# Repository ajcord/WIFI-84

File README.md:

# WIFI-84
*Wi-Fi Interface Furnishing Internet for TI-84*

## Overview

This project aims to provide direct Internet access to TI-84 calculators
using an inexpensive ESP8266 module as a wireless modem.
It supports calculators with I/O ports, i.e. those up to the TI-84+CSE.

## Architecture

The project consists of four main parts:

1. A physical interface between the calculator and ESP8266
2. A driver for communicating between them
3. A high-level networking API exposed to calculator programs
4. A small collection of sample utilities using the API

### Physical interface

The adapter is powered from the calculator's USB port for convenience.
It could probably also be powered from e.g. a USB phone charger,
as long as the power supply is not noisy.
The USB's 5V gets converted to 3.3V using an efficient switching regulator
to save battery.

For communication, the adapter uses the I/O port for simplicity.
Ideally, it would use the USB port for forward compatibility and since
it already uses it for power;
however, writing a USB driver would be a lot of effort for very little gain,
considering that the TI-84+CE uses a completely different USB controller.

It would be nice to have the adapter plug directly into the calculator,
but I can't seem to find any 2.5mm male headphone connectors,
and the only USB mini-B male connector I found is vertical.
Instead, the adapter plugs in using cables,
but is laid out to make it easy to switch to a plug-oriented design later.
See the `hardware` folder for the schematic and circuit board.

### Driver

The ESP8266 runs firmware that directly communicates with the calculator
using the [ArTICL](https://github.com/KermMartian/ArTICL) library.
It acts as a CBL2 device to make communication easy with TI Basic programs.

The calculator does not need a driver since it uses the CBL2
Get( and Send( commands.
It does, however, need a way to turn on and off the USB port.

### API

The API exposed to the calculator is still in flux,
but it will provide similar capabilities to the ESP8266's default AT firmware.
The calculator will be able to send string variables containing API calls,
and then it will request another variable to get the result (if applicable).

The calculator will send token strings as commands
in order to save program space.
The ESP8266 will respond with token strings or real numbers,
depending on the call.

### Utilities

There will need to be a program to allow the user to connect to
nearby Wi-Fi networks.
It can be as simple as a menu of SSIDs.
By including such a program, applications won't need to
reinvent the wheel, and the connection can be managed centrally.

Also, a tool like wget/curl would be useful for testing.
It would probably have to include its own viewer to display the response
incrementally due to limited RAM.
For HTML, maybe it could have the option to display it with tags stripped
so that it looks sort of like a webpage.

In the future, it would be really cool to have the ESP8266 pre-render webpages
and have the calculator display them screen by screen.
A Slack client would also be neat.

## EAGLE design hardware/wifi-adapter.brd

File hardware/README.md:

# Hardware

## Schematic

See `wifi-adapter.sch` for the schematic,
or `wifi-adapter.pdf` if you don't have EAGLE.

## Bill of Materials

This DigiKey cart contains all the components needed in the project:
[cart](http://www.digikey.com/short/3r35nm)

In addition, you will need to manufacture a circuit board using
`wifi-adapter.brd`.
[OSH Park](https://oshpark.com) is a good place to order it.

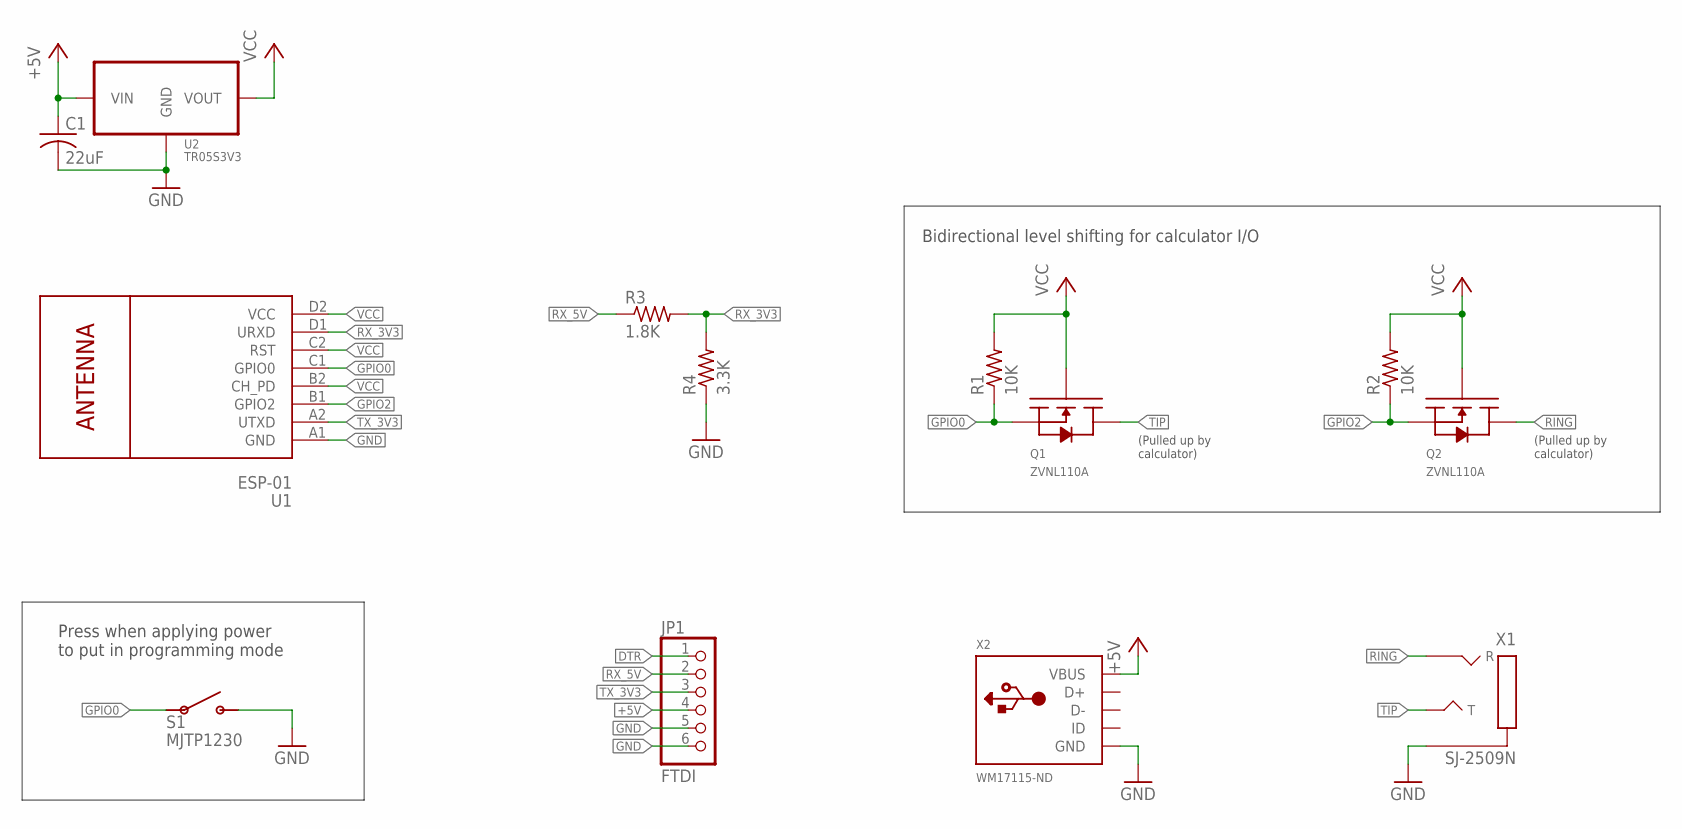
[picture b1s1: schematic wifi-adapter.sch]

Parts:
C1: 22uF; C025-025X050
JP1: FTDI; 1X06
Q1, Q2: ZVNL110A; E-LINE-RA
R1, R2: 10K; 0207/10
R3: 1.8K; 0207/10
R4: 3.3K; 0207/10
S1: MJTP1230; TACTILE-BUTTON-MJTP1230
U1: ESP-01; WIRELESS-WIFI-ESP-01
U2: TR05S3V3; 3-SIP
X1: SJ-2509N
X2: WM17115-ND; USB-MINI-B

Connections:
+5V: C1.1, JP1.4, U2.P$1 (VIN), X2.VBUS
DTR: JP1.1
GND: C1.2, JP1.5, JP1.6, R4.1, S1.P$2 (3), S1.P$4 (3), U1.A1 (GND), U2.P$2 (GND), X1.P$1, X2.GND, X2.GND1 (GND), X2.GND4 (GND)
GPIO0: Q1.P$3 (S), R1.1, S1.P$1 (1), S1.P$3 (1), U1.C1 (GPIO0)
GPIO2: Q2.P$3 (S), R2.1, U1.B1 (GPIO2)
RING: Q2.P$1 (D), X1.P$2
RX_3V3: R3.2, R4.2, U1.D1 (URXD)
RX_5V: JP1.2, R3.1
TIP: Q1.P$1 (D), X1.P$3
TX_3V3: JP1.3, U1.A2 (UTXD)
VCC: Q1.P$2 (G), Q2.P$2 (G), R1.2, R2.2, U1.B2 (CH_PD), U1.C2 (RST), U1.D2 (VCC), U2.P$3 (VOUT)

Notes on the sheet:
(Pulled up by calculator)
Bidirectional level shifting for calculator I/O
Press when applying power to put in programming mode

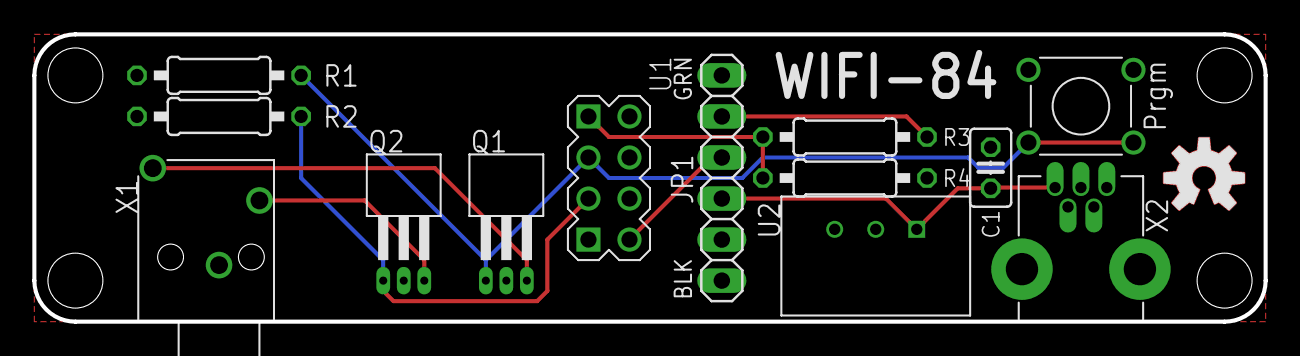
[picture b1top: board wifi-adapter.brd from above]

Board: 2 copper layers, 76.2 x 17.8 mm, 15 parts (0 on the bottom side), 10 nets.

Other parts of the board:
U$1: OSHW-LOGO-M
U$2: OSHW-LOGO-M_COPPER

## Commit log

2016-12-30 Updated architecture ideas
2017-01-02 First real commit
2017-01-03 Improved CSV generation
2017-01-03 Greatly simplified token parsing by assuming tokens are valid and removing toString
2017-01-03 Removed unnecessary datalen
2017-01-03 Fixed Connected to return 1 or 0, not enum
2017-01-03 Enum-ified token prefixes
2017-01-03 Fixed parameter name
2017-01-03 Added a token string builder
2017-01-03 Use StringBuilder instead of hacky stuff
2017-01-03 Rename insert() to append() for clarity
2017-01-03 Added length checking to StringBuilder
2017-01-03 Moved token list to separate file
2017-01-03 Fixed token casting
2017-01-03 Compacted case statements
2017-01-03 Switched to unsigned chars
2017-01-03 Fixed a couple of character conversion mistakes
2017-01-04 Removed StringBuilder
2017-01-04 Minor style changes
2017-01-04 Added some debug printing
2017-01-04 Added ability to connect to a network
2017-01-04 Made Connected return more detailed information
2017-01-04 Added comments and tweaked API
2017-01-04 Added basic TCP and UDP client commands
2017-01-04 Switched tokens for sending/receiving on a connection
2017-01-04 Added HTTP GET
2017-01-04 Fixed String conversion
2017-01-04 Added debugging output
2017-01-04 Added ability to see which network is connected to
2017-01-05 Added connection management program
2017-01-06 Added timeout, default to current network, and fixed syntax errors
2017-01-08 Added HTTP POST
2017-01-08 Added basic wget utility
2017-01-08 Added simplistic HTML viewer

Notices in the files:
parts and their libraries:
diy-modules: Released under the Creative Commons Attribution 4.0 International License: http://creativecommons.org/licenses/by/4.0
SparkFun-Aesthetics: Licensing: Creative Commons ShareAlike 4.0 International - https://creativecommons.org/licenses/by-sa/4.0
